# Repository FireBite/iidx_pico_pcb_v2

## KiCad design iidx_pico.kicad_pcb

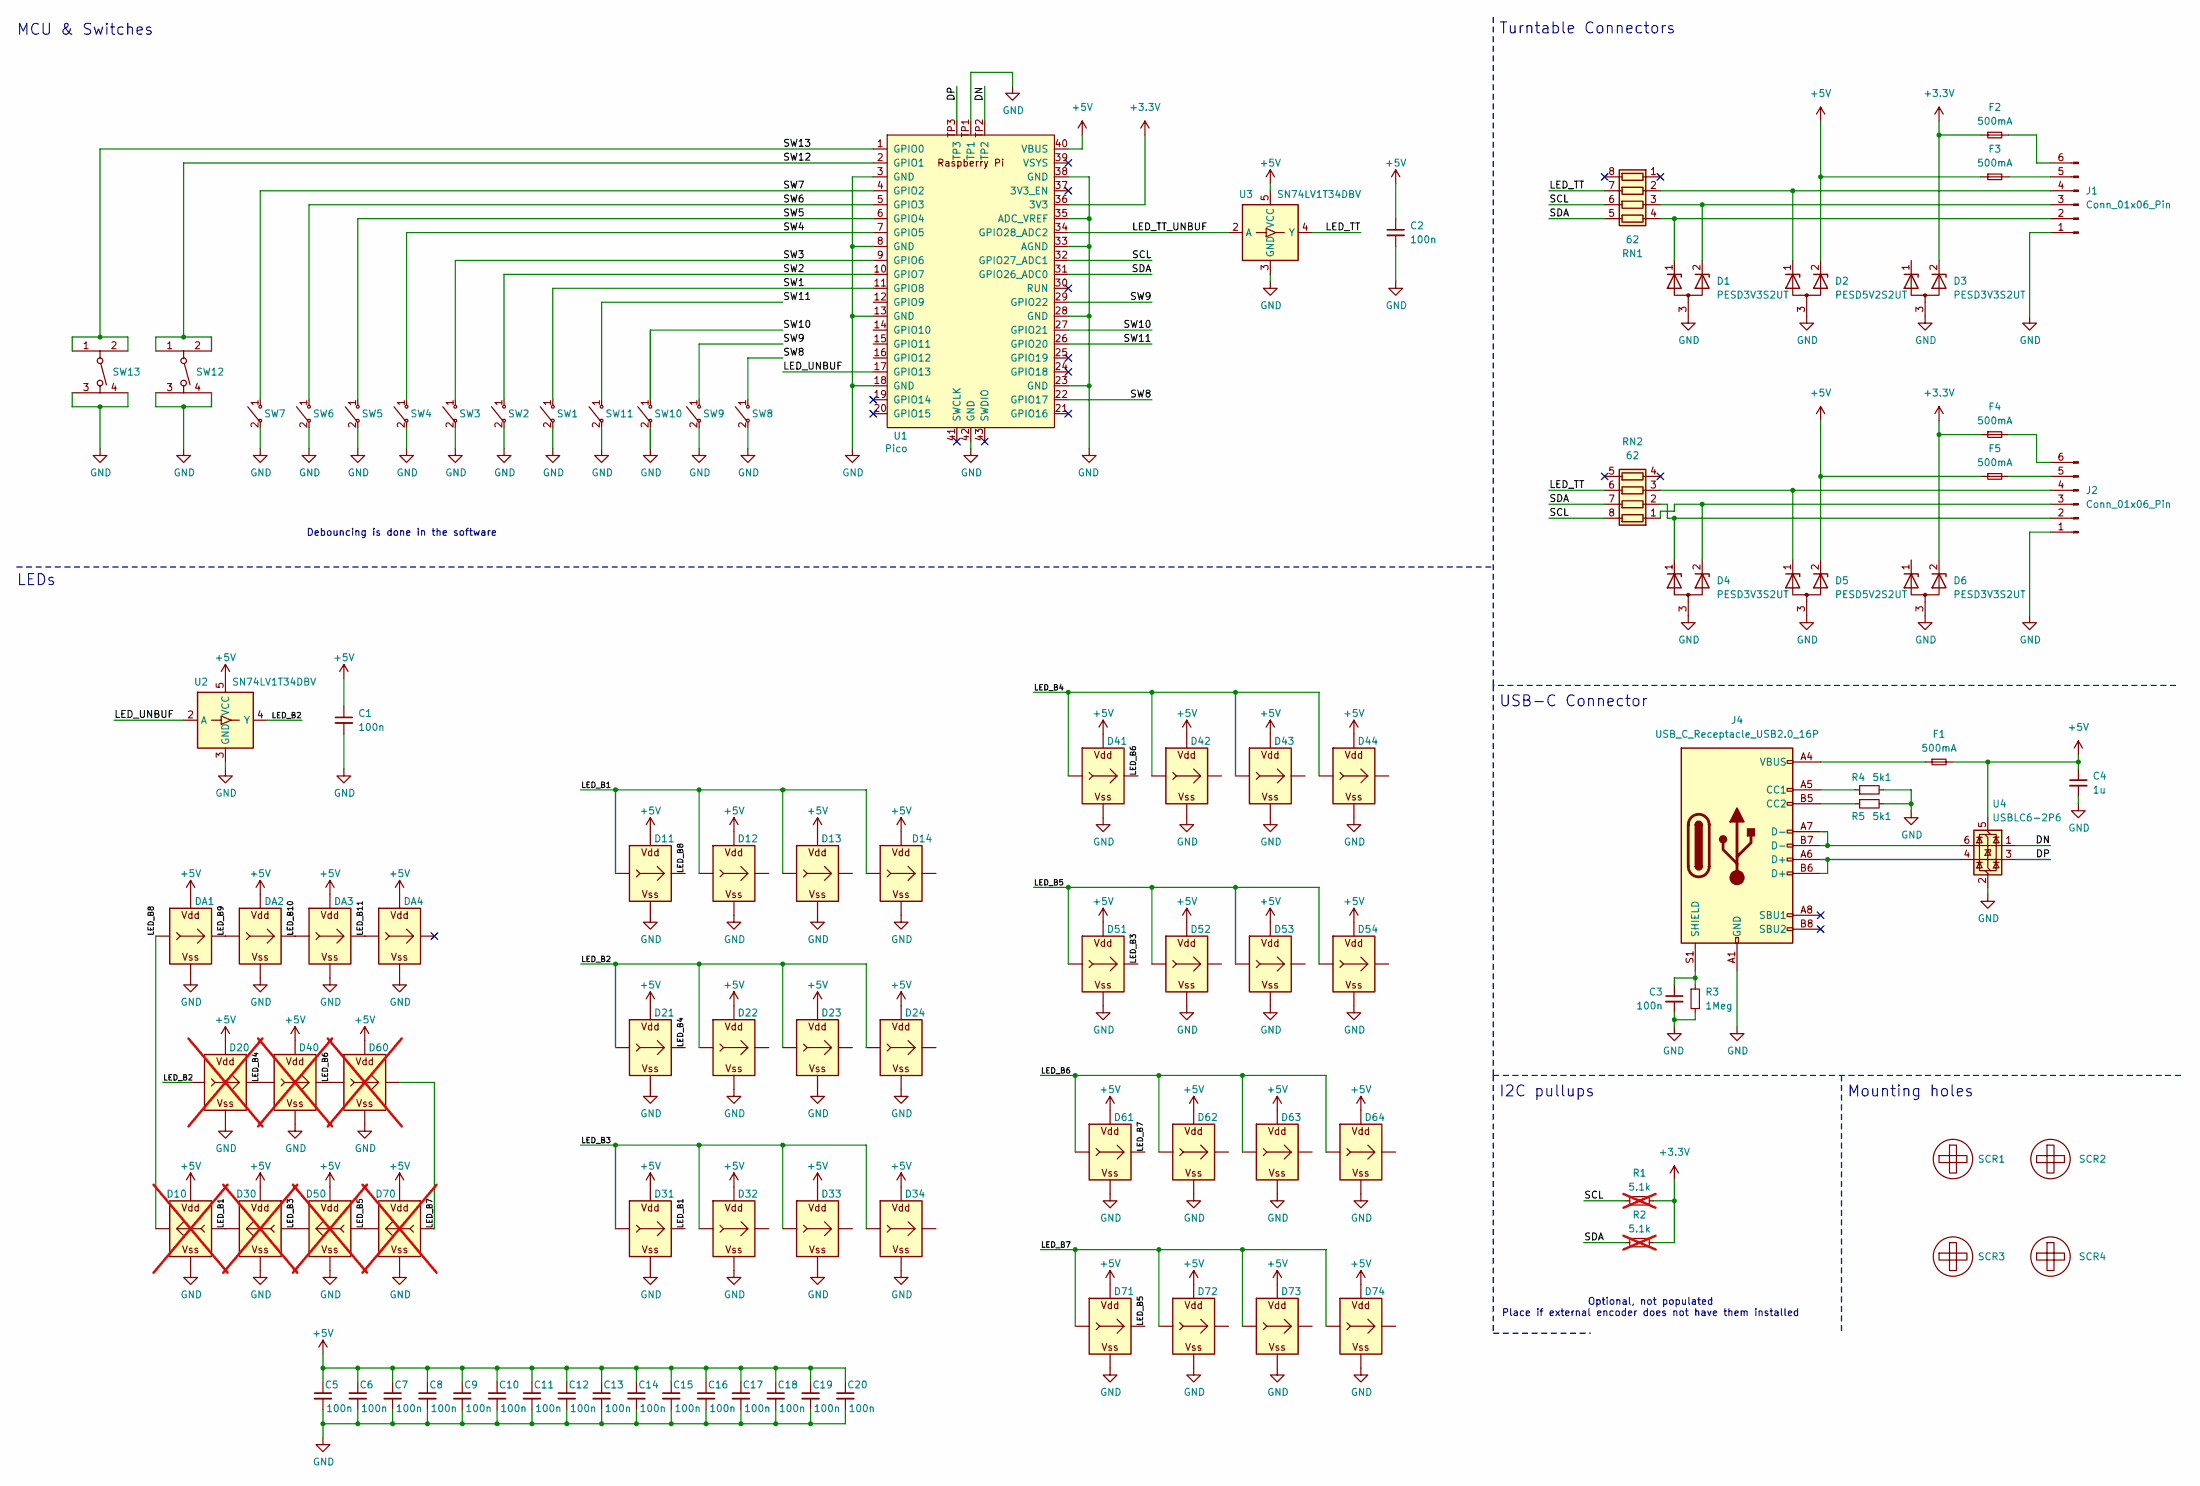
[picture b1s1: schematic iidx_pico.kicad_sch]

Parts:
C1, C2, C3, C5, C6, C7, C8, C9, C10, C11, C12, C13, C14, C15, C16, C17, C18, C19, C20: 100n; C_0603_1608Metric; LCSC C14663
C4: 1u; C_0805_2012Metric; LCSC C28323
D1, D3, D4, D6: PESD3V3S2UT; SOT-23; LCSC C84276
D2, D5: PESD5V2S2UT; SOT-23; LCSC C18441
D10, D20, D30, D40, D50, D60, D70: WS2812B_Unified; WS2812B-2835; not fitted
D11, D12, D13, D14, D21, D22, D23, D24, D31, D32, D33, D34, D41, D42, D43, D44, D51, D52, D53, D54, D61, D62, D63, D64, D71, D72, D73, D74: WS2812B_Unified; WS2812B-1615; LCSC C965555
DA1, DA2, DA3, DA4: WS2812B_Unified; WS2812B-2835; LCSC C965555
F1, F2, F3, F4, F5: 500mA; Fuse_0805_2012Metric; LCSC C7501939
J1, J2: Conn_01x06_Pin; JST_GH_SM06B-GHS-TB_1x06-1MP_P1.25mm_Horizontal; LCSC C133065
J4: USB_C_Receptacle_USB2.0_16P; USB_C_Receptacle_GCT_USB4085; LCSC C7095263
R1, R2: 5.1k; R_0603_1608Metric; LCSC C105580; not fitted
R3: 1Meg; R_0603_1608Metric; LCSC C105578
R4, R5: 5k1; R_0603_1608Metric; LCSC C105580
RN1, RN2: 62; R_Array_Convex_4x0603; LCSC C728917
SCR1, SCR2, SCR3, SCR4: ScrewHole; MountingHole_3.2mm_M3
SW1, SW2, SW3, SW4, SW5, SW6, SW7: SWITCH_SPST; SW_Kailh_Choc_V1V2_IIDX
SW8, SW9, SW10, SW11: SWITCH_SPST; SW_Kailh_Choc_V1V2_1.00u_LED
SW12, SW13: Tact_4pin; EVQP1K05M; LCSC C2915185
U1: Pico; RPi_Pico_SMD; LCSC C7203002
U2, U3: SN74LV1T34DBV; SOT-23-5; LCSC C100024
U4: USBLC6-2P6; SOT-23-6; LCSC C7519

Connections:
+3.3V: D3.2 (K), D6.2 (K), F2.1, F4.1, R1.2, R2.2, U1.36 (3V3)
+5V: C1.1, C2.1, C4.1, C5.1, C6.1, C7.1, C8.1, C9.1, C10.1, C11.1, C12.1, C13.1, C14.1, C15.1, C16.1, C17.1, C18.1, C19.1, C20.1, D2.2 (K), D5.2 (K), D10.V (VDD), D11.V (VDD), D12.V (VDD), D13.V (VDD), D14.V (VDD), D20.V (VDD), D21.V (VDD), D22.V (VDD), D23.V (VDD), D24.V (VDD), D30.V (VDD), D31.V (VDD), D32.V (VDD), D33.V (VDD), D34.V (VDD), D40.V (VDD), D41.V (VDD), D42.V (VDD), D43.V (VDD), D44.V (VDD), D50.V (VDD), D51.V (VDD), D52.V (VDD), D53.V (VDD), D54.V (VDD), D60.V (VDD), D61.V (VDD), D62.V (VDD), D63.V (VDD), D64.V (VDD), D70.V (VDD), D71.V (VDD), D72.V (VDD), D73.V (VDD), D74.V (VDD), DA1.V (VDD), DA2.V (VDD), DA3.V (VDD), DA4.V (VDD), F1.2, F3.1, F5.1, U1.40 (VBUS), U2.5 (VCC), U3.5 (VCC), U4.5 (VBUS)
/DN: U1.TP2, U4.1 (I/O1)
/DP: U1.TP3, U4.3 (I/O2)
/LED_B1: D10.I (In), D11.I (In), D12.I (In), D13.I (In), D14.I (In), D30.O (Out), D31.O (Out)
/LED_B2: D20.I (In), D21.I (In), D22.I (In), D23.I (In), D24.I (In), U2.4 (Y)
/LED_B3: D30.I (In), D31.I (In), D32.I (In), D33.I (In), D34.I (In), D50.O (Out), D51.O (Out)
/LED_B4: D20.O (Out), D21.O (Out), D40.I (In), D41.I (In), D42.I (In), D43.I (In), D44.I (In)
/LED_B5: D50.I (In), D51.I (In), D52.I (In), D53.I (In), D54.I (In), D70.O (Out), D71.O (Out)
/LED_B6: D40.O (Out), D41.O (Out), D60.I (In), D61.I (In), D62.I (In), D63.I (In), D64.I (In)
/LED_B7: D60.O (Out), D61.O (Out), D70.I (In), D71.I (In), D72.I (In), D73.I (In), D74.I (In)
/LED_B8: D10.O (Out), D11.O (Out), DA1.I (In)
/LED_B9: DA1.O (Out), DA2.I (In)
/LED_B10: DA2.O (Out), DA3.I (In)
/LED_B11: DA3.O (Out), DA4.I (In)
/LED_TT: RN1.7 (R2.2), RN2.6 (R3.2), U3.4 (Y)
/LED_TT_UNBUF: U1.34 (GPIO28_ADC2), U3.2 (A)
/LED_UNBUF: U1.17 (GPIO13), U2.2 (A)
/SCL: R1.1, RN1.6 (R3.2), RN2.8 (R1.2), U1.32 (GPIO27_ADC1)
/SDA: R2.1, RN1.5 (R4.2), RN2.7 (R2.2), U1.31 (GPIO26_ADC0)
/SW1: SW1.1 ("~"), U1.11 (GPIO8)
/SW2: SW2.1 ("~"), U1.10 (GPIO7)
/SW3: SW3.1 ("~"), U1.9 (GPIO6)
/SW4: SW4.1 ("~"), U1.7 (GPIO5)
/SW5: SW5.1 ("~"), U1.6 (GPIO4)
/SW6: SW6.1 ("~"), U1.5 (GPIO3)
/SW7: SW7.1 ("~"), U1.4 (GPIO2)
/SW8: SW8.1 ("~"), U1.22 (GPIO17)
/SW9: SW9.1 ("~"), U1.29 (GPIO22)
/SW10: SW10.1 ("~"), U1.27 (GPIO21)
/SW11: SW11.1 ("~"), U1.26 (GPIO20)
/SW12: SW12.1, SW12.2, U1.2 (GPIO1)
/SW13: SW13.1, SW13.2, U1.1 (GPIO0)
GND: C1.2, C2.2, C3.2, C4.2, C5.2, C6.2, C7.2, C8.2, C9.2, C10.2, C11.2, C12.2, C13.2, C14.2, C15.2, C16.2, C17.2, C18.2, C19.2, C20.2, D1.3 (A), D2.3 (A), D3.3 (A), D4.3 (A), D5.3 (A), D6.3 (A), D10.G (VSS), D11.G (VSS), D12.G (VSS), D13.G (VSS), D14.G (VSS), D20.G (VSS), D21.G (VSS), D22.G (VSS), D23.G (VSS), D24.G (VSS), D30.G (VSS), D31.G (VSS), D32.G (VSS), D33.G (VSS), D34.G (VSS), D40.G (VSS), D41.G (VSS), D42.G (VSS), D43.G (VSS), D44.G (VSS), D50.G (VSS), D51.G (VSS), D52.G (VSS), D53.G (VSS), D54.G (VSS), D60.G (VSS), D61.G (VSS), D62.G (VSS), D63.G (VSS), D64.G (VSS), D70.G (VSS), D71.G (VSS), D72.G (VSS), D73.G (VSS), D74.G (VSS), DA1.G (VSS), DA2.G (VSS), DA3.G (VSS), DA4.G (VSS), J1.1, J2.1, J4.A1 (GND), J4.A12 (GND), J4.B1 (GND), J4.B12 (GND), R3.2, R4.2, R5.2, SW1.2 ("~"), SW2.2 ("~"), SW3.2 ("~"), SW4.2 ("~"), SW5.2 ("~"), SW6.2 ("~"), SW7.2 ("~"), SW8.2 ("~"), SW9.2 ("~"), SW10.2 ("~"), SW11.2 ("~"), SW12.3, SW12.4, SW13.3, SW13.4, U1.3 (GND), U1.8 (GND), U1.13 (GND), U1.18 (GND), U1.23 (GND), U1.28 (GND), U1.33 (AGND), U1.35 (ADC_VREF), U1.38 (GND), U1.42 (GND), U1.TP1, U2.3 (GND), U3.3 (GND), U4.2 (GND)
unnamed: F1.1, J4.A4 (VBUS), J4.A9 (VBUS), J4.B4 (VBUS), J4.B9 (VBUS)
unnamed: D1.1 (K), J1.2, RN1.4 (R4.1)
unnamed: D1.2 (K), J1.3, RN1.3 (R3.1)
unnamed: D2.1 (K), J1.4, RN1.2 (R2.1)
unnamed: F3.2, J1.5
unnamed: F2.2, J1.6
unnamed: D4.1 (K), J2.2, RN2.2 (R2.1)
unnamed: D4.2 (K), J2.3, RN2.1 (R1.1)
unnamed: D5.1 (K), J2.4, RN2.3 (R3.1)
unnamed: F5.2, J2.5
unnamed: F4.2, J2.6
unnamed: J4.A5 (CC1), R4.1
unnamed: J4.B5 (CC2), R5.1
unnamed: J4.A6 (D+), J4.B6 (D+), U4.4 (I/O2)
unnamed: J4.A7 (D-), J4.B7 (D-), U4.6 (I/O1)
unnamed: C3.1, J4.S1 (SHIELD), R3.1

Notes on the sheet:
MCU & Switches
Mounting holes
Optional, not populated Place if external encoder does not have them installed
Debouncing is done in the software
Turntable Connectors
LEDs
USB-C Connector
I2C pullups

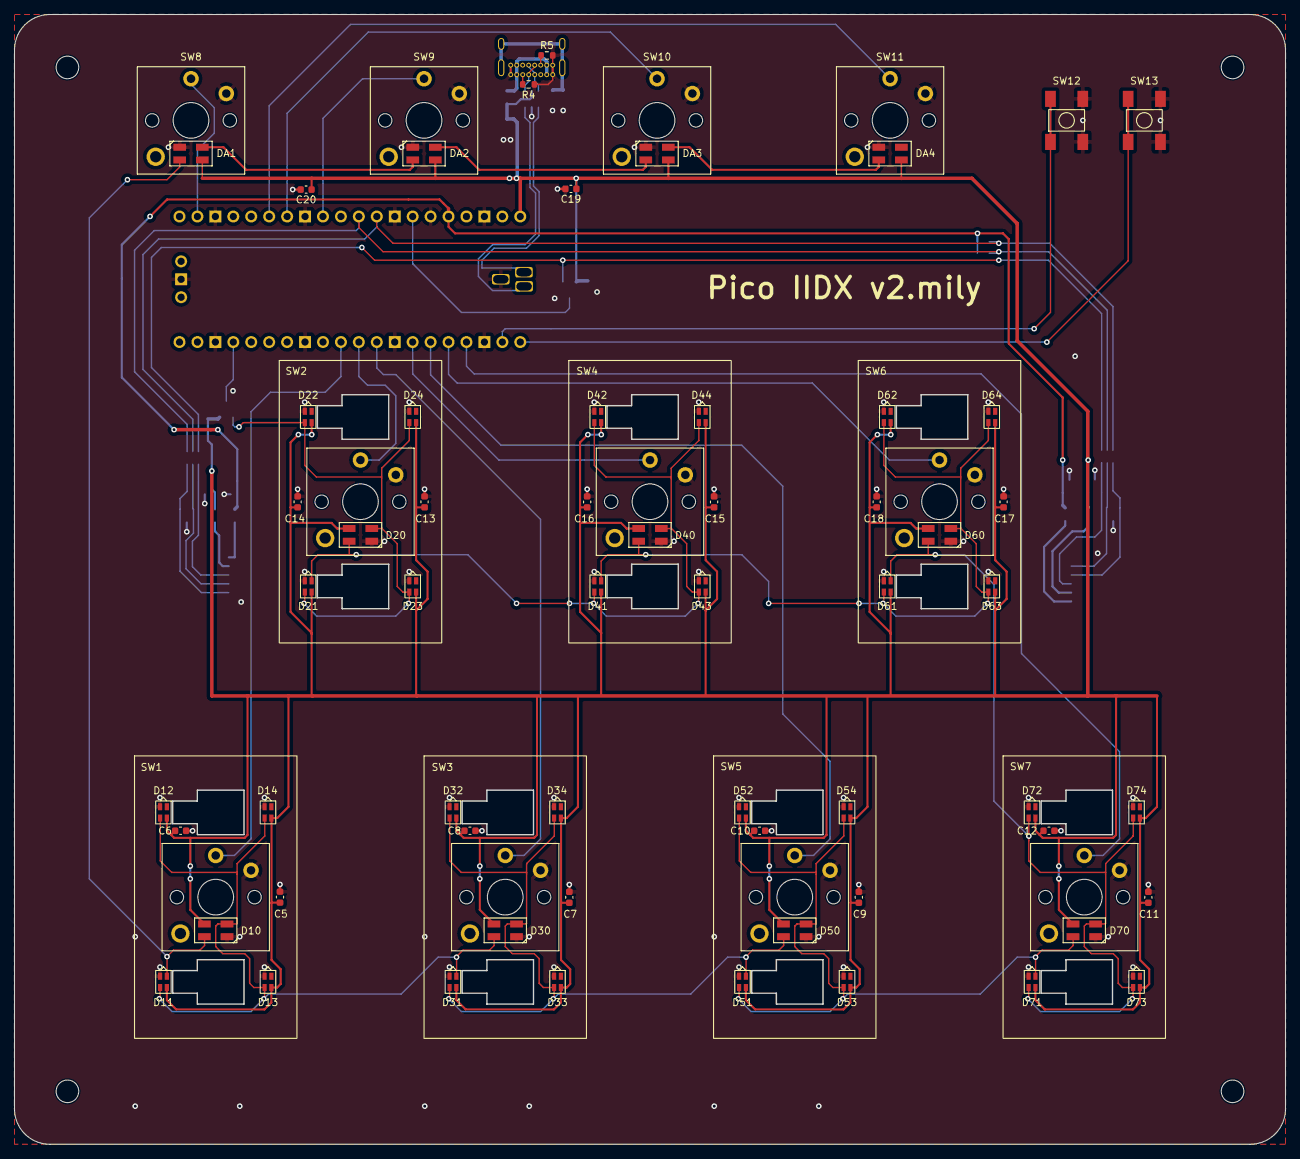
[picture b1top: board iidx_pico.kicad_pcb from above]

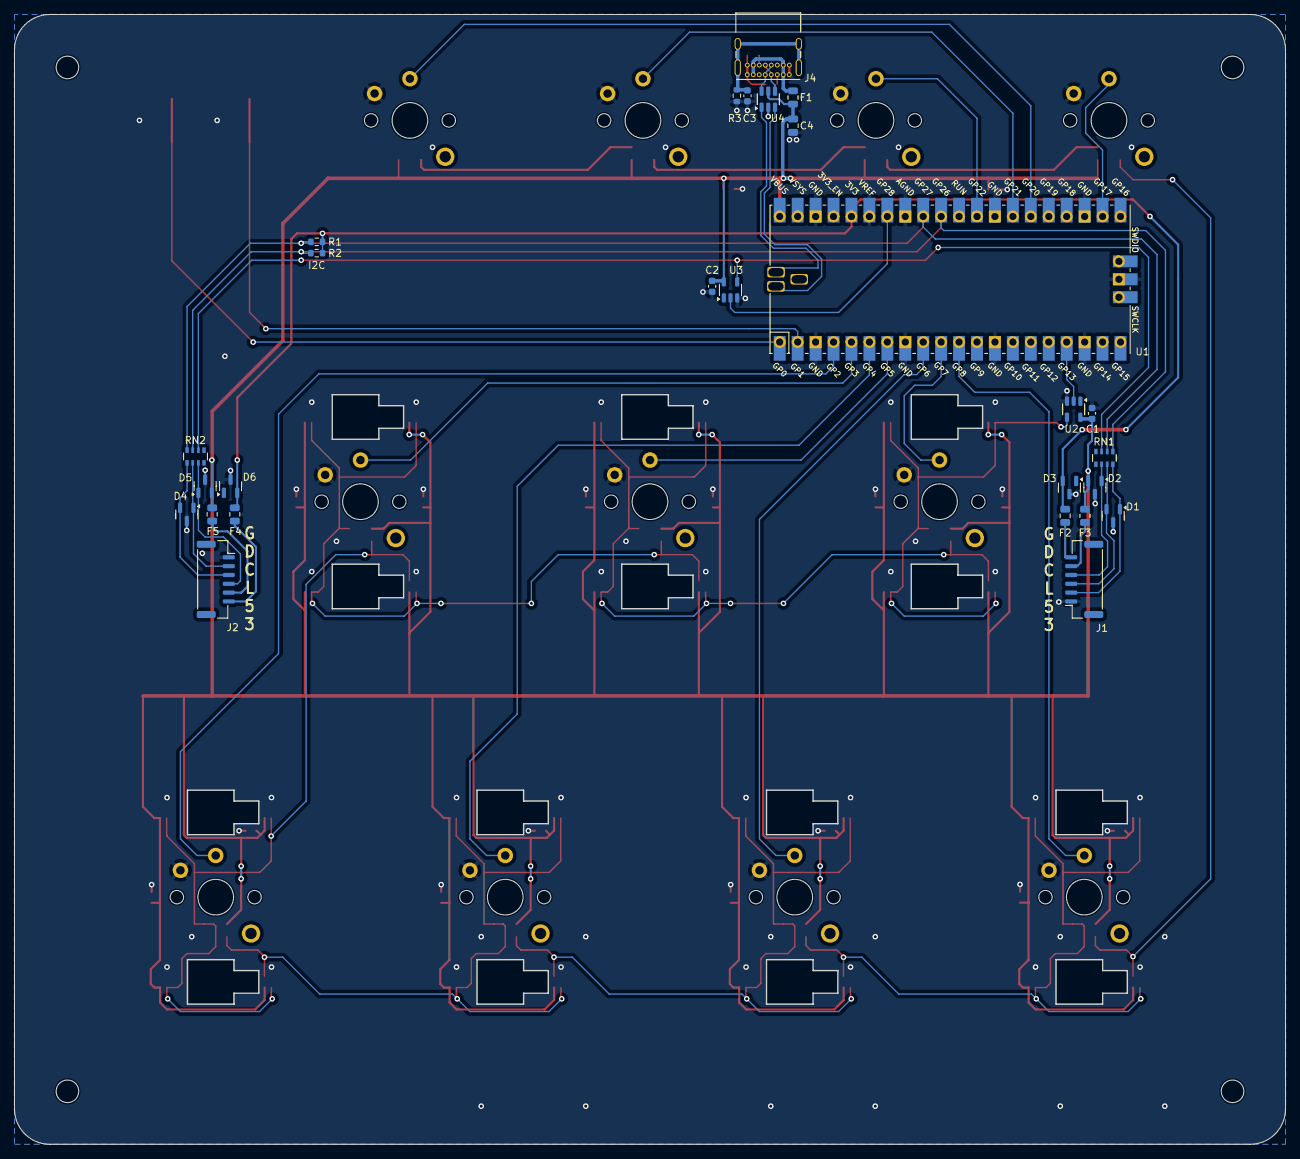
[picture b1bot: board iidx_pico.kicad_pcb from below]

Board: 2 copper layers, 180.0 x 160.0 mm, 101 parts (27 on the bottom side), 50 nets.
